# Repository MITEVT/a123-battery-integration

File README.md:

# a123-battery-integration
Battery Management System for A123 Battery-Brusa Charger combination.
## Target
NXP LPC11Cxx series ARM Cortex-M0
## Description
Interfaces between A123 Module CAN Bus and Brusa CAN Bus and sets appropriate voltage and current profiles. Essentially a battery control module.
### Referenced Library Files
* [EVT's LPC11xx Library](https://github.com/MITEVT/lpc11cx4-library)
* [Unity](https://github.com/ThrowTheSwitch/Unity)

### Requirements
```
gcc-arm-none-eabi
doxygen
oclint
```

### Looking for Examples?
* [EVT's LPC11xx Library](https://github.com/MITEVT/lpc11cx4-library)

### Trying to configure sysinit.c?
Use CMSIS Configuration Wizard v0.0.6
* http://helmpcb.com/software/cmsis-configuration-wizard
* https://sourceforge.net/projects/cmsisconfig/

## More info about our team
http://web.mit.edu/evt/

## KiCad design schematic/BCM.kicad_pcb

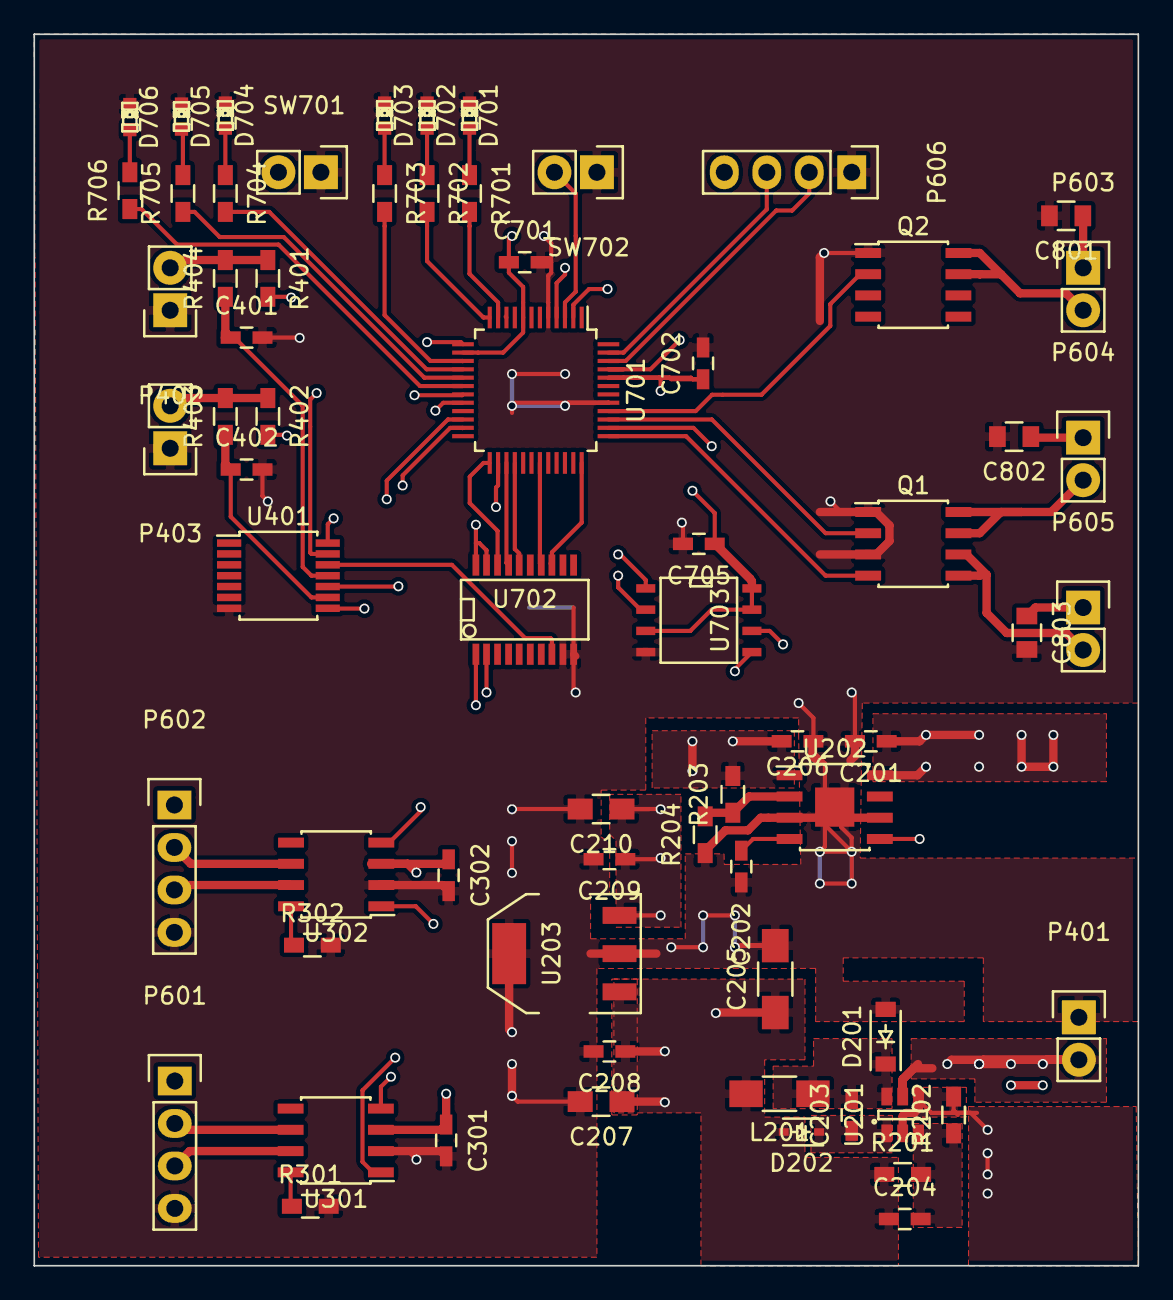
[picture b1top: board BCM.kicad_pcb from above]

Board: 4 copper layers, 66.0 x 73.7 mm, 67 parts (0 on the bottom side), 59 nets.

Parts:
C201, C206, C401, C402: 1uF; C_0603_HandSoldering
C202: 10nF; C_0603_HandSoldering
C203: 0.22pF; C_0603_HandSoldering
C204: 10pF; C_0603_HandSoldering
C205: 100uF; C_1206_HandSoldering
C207, C210: 10u; C_0805_HandSoldering
C208, C209, C701, C702: 100n; C_0603_HandSoldering
C301, C302, C705: 0.1uF; C_0603_HandSoldering
C801, C802, C803: 10uF; C_0805
D201: MBR0540; SOD-123
D202: CMDSH-3; SOD-323
D701, D702, D703, D704, D705, D706: RED; LED-0603
L201: 47uH; C_1206_HandSoldering
P401: POWERCON; Pin_Header_Straight_1x02
P402: KEYSWITCH; Pin_Header_Straight_1x02
P403: CHARGESW; Pin_Header_Straight_1x02
P601: BRUSA_CANCON; Pin_Header_Straight_1x04
P602: A123_CANCON; Pin_Header_Straight_1x04
P603: CON+; Pin_Header_Straight_1x02
P604: CON-; Pin_Header_Straight_1x02
P605: CONPRE; Pin_Header_Straight_1x02
P606: UART; Pin_Header_Straight_1x04
Q1, Q2: IRF7101PbF; SOIC-8_3.9x4.9mm_Pitch1.27mm
R201: 1M; R_0603_HandSoldering
R202: 604K; R_0603_HandSoldering
R203: 88.7k; R_0603_HandSoldering
R204: 10k; R_0603_HandSoldering
R301, R302: 33k; R_0603_HandSoldering
R401, R402, R403, R404: 20k; R_0603_HandSoldering
R701, R702, R703, R704, R705, R706: 1k; R_0603_HandSoldering
SW701: ISP; Pin_Header_Straight_1x02
SW702: RESET; Pin_Header_Straight_1x02
U201: LT1934; SOT-23-6
U202: ADP7105; SOIC-8-1EP_3.9x4.9mm_Pitch1.27mm
U203: SPX2920M3-3.3; SOT-223
U301, U302: MCP2551-I/SN; SOIC-8_3.9x4.9mm_Pitch1.27mm
U401: 74LS14; TSSOP-14_4.4x5mm_Pitch0.65mm
U701: LPC11C14; LQFP-48_7x7mm_Pitch0.5mm
U702: MCP2515_TSSOP; SSOP-20
U703: AT25XX; SOIC-8-N

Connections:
+3V3: C209.1, C210.1, C701.1, C702.1, C705.1, R401.2, R402.2, U203.3, U401.14, U701.8, U701.14, U701.44, U702.19, U702.20, U703.3, U703.7, U703.8
+5V: C204.1, C205.1, C207.1, C208.1, C301.1, C302.1, D202.2, L201.2, P606.4, R201.1, U203.1, U301.3, U302.3
+12V: C206.1, P602.1, R203.1, U202.1
+15V: C201.1, C801.1, C802.1, C803.1, P401.2, P603.1, P604.1, P605.1, U201.5, U202.8
/Can transceiver/CAN1_H_I: P601.2, U301.6
/Can transceiver/CAN1_L_I: P601.3, U301.7
/Can transceiver/CAN1_RS: R301.1, U301.8
/Can transceiver/CAN1_RX: U301.4, U702.2
/Can transceiver/CAN1_TX: U301.1, U702.1
/Can transceiver/CAN2_H_I: P602.2, U302.6
/Can transceiver/CAN2_L_I: P602.3, U302.7
/Can transceiver/CAN2_RS: R302.1, U302.8
/Can transceiver/CAN2_RX: U302.4, U701.19
/Can transceiver/CAN2_TX: U302.1, U701.20
/Contactor Driver/CON+: Q2.2, U701.40
/Contactor Driver/CON+_LOW: P603.2, Q2.7, Q2.8
/Contactor Driver/CON-: Q1.2, U701.39
/Contactor Driver/CON-_LOW: P604.2, Q1.7, Q1.8
/Contactor Driver/CONPRE: Q1.4, U701.37
/Contactor Driver/CONPRE_LOW: P605.2, Q1.5, Q1.6
/Input Connectors/CHARGESWITCH_R: P403.2, R402.1, R403.2
/Input Connectors/CHARGESWITCH_RC: C402.1, R403.1, U401.9
/Input Connectors/KEYSKWITCH_RC: C401.1, R404.1, U401.11
/Input Connectors/KEYSWITCH_R: P402.2, R401.1, R404.2
/Power/5V0_BOOST: C203.1, D202.1, U201.1
/Power/5V0_FB: C204.2, R201.2, R202.1, U201.3
/Power/5V0_L: C203.2, D201.1, L201.1, U201.6
/Power/12V0_FB: R203.2, R204.1, U202.2
/Power/12V0_SS: C202.1, U202.4
/Power/EN12V0: U202.5, U701.45
/microController/CAN1_INT: U701.36, U702.13
/microController/CAN1_MISO: U701.27, U702.17
/microController/CAN1_MOSI: U701.28, U702.16
/microController/CAN1_SCK: U701.31, U702.14
/microController/CAN1_SSEL: U701.25, U702.18
/microController/CAN_OSC2: U401.12, U702.8
/microController/CHARGESWITCH_IN: U401.8, U701.22
/microController/CLKOUT: SW701.2, U401.13, U701.4
/microController/IO_LED0: R701.2, U701.11
/microController/IO_LED1: R702.2, U701.12
/microController/IO_LED2: R703.2, U701.15
/microController/IO_LED3: R704.2, U701.16
/microController/IO_LED4: R705.1, U701.17
/microController/IO_LED5: R706.1, U701.18
/microController/KEYSWITCH_IN: U401.10, U701.23
/microController/MCU_RESET: SW702.2, U701.3
/microController/MCU_RXD: P606.2, U701.46
/microController/MCU_TXD: P606.3, U701.47
/microController/PROM_MISO: U701.26, U703.2
/microController/PROM_MOSI: U701.38, U703.5
/microController/PROM_SCK: U701.13, U703.6
/microController/PROM_SSEL: U701.2, U703.1
GND: C201.2, C202.2, C205.2, C206.2, C207.2, C208.2, C209.2, C210.2, C301.2, C302.2, C401.2, C402.2, C701.2, C702.2, C705.2, C801.2, C802.2, C803.2, D201.2, D701.1, D702.1, D703.1, D704.1, D705.1, D706.1, P401.1, P402.1, P403.1, P601.4, P602.4, P606.1, Q1.1, Q1.3, Q2.1, R202.2, R204.2, R301.2, R302.2, SW701.1, SW702.1, U201.2, U201.4, U202.3, U202.6, U202.9, U203.2, U203.4, U301.2, U302.2, U401.7, U701.5, U701.41, U702.9, U702.10, U703.4
unnamed: D701.2, R701.1
unnamed: D702.2, R702.1
unnamed: D703.2, R703.1
unnamed: D704.2, R704.1
unnamed: D705.2, R705.2
unnamed: D706.2, R706.2

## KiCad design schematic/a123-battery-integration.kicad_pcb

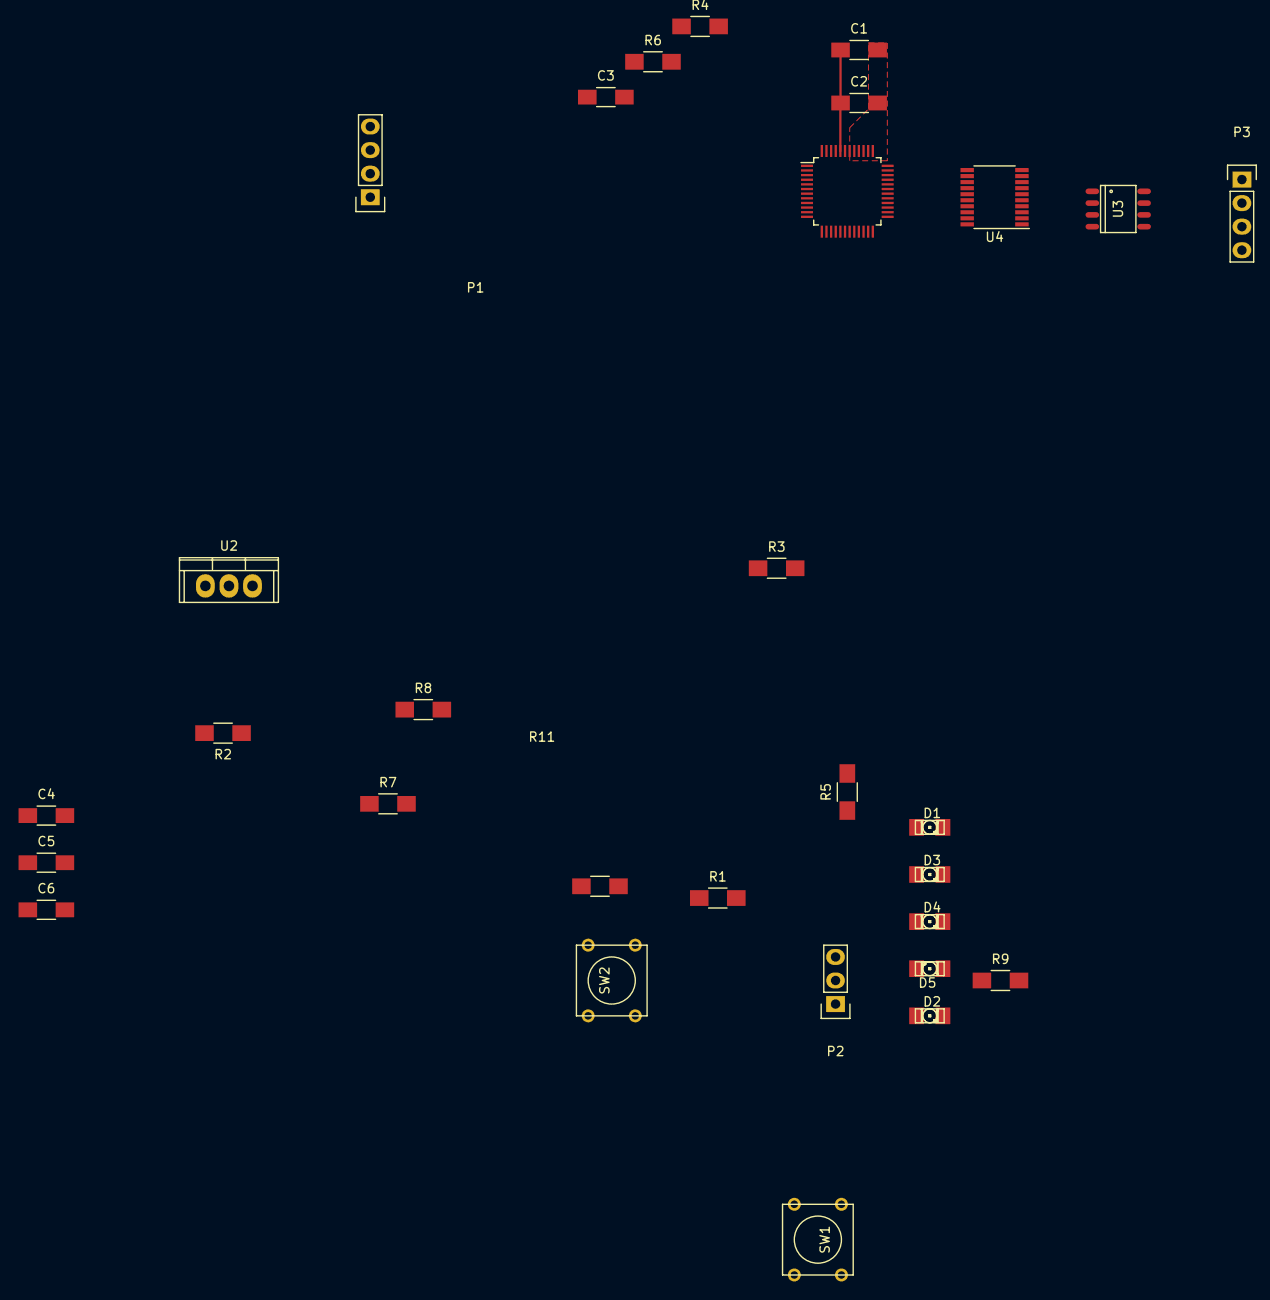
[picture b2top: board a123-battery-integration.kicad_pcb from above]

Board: 2 copper layers, 30 parts (0 on the bottom side), 30 nets.

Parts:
C1, C2, C5, C6: 10nF; C_1206_HandSoldering
C3, C4: 100nF; C_1206_HandSoldering
D1, D2, D3, D4, D5: LED; LED-1206
P1, P3: CONN_01X04; Pin_Header_Straight_1x04
P2: CONN_01X03; Pin_Header_Straight_1x03
R1: 4.7k; R_1206_HandSoldering
R2: 100; R_1206_HandSoldering
R3, R11: 120; R_1206_HandSoldering
R4, R5, R6, R7, R8: 82; R_1206_HandSoldering
R9: 10k; R_1206_HandSoldering
SW1, SW2: SW_PUSH; SW_PUSH_SMALL
U1: LPC11C24; TQFP-48_7x7mm_Pitch0.5mm
U2: LM1084IT-3.3/NOPB; TO-220
U3: ISO1050; SO-8
U4: MCP2515_TSSOP; TSSOP-20_4.4x6.5mm_Pitch0.65mm

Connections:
+3.3VP: C1.1, C2.1, C4.1, C5.1, C6.1, P1.1, R1.1, R2.1, R9.1, U1.8, U1.14, U1.17, U1.20, U1.44, U2.2, U3.1, U4.20
+5V: C3.1, U2.3
/CAN_IFACE_MISO: U1.27, U4.17
/CAN_IFACE_MOSI: U1.28, U4.16
/CAN_IFACE_SCK: U1.31, U4.14
/CAN_TRAN_RXD: U3.2, U4.2
/CAN_TRAN_TXD: U3.3, U4.1
/ISO_5V: P3.1, U3.8
/ISO_CANH: P3.2, R11.2, U3.7
/ISO_CANL: P3.3, R11.1, U3.6
/ISO_GND: P3.4, U3.5
/MCU_LED0: R5.2, U1.36
/MCU_LED1: R6.2, U1.37
/MCU_LED2: R7.2, U1.43
/MCU_LED3: R8.2, U1.48
/MCU_LED10: R4.2, U1.25
/MCU_SERIAL_RXD: P1.3, U1.46
/MCU_SERIAL_TXD: P1.4, U1.47
GND: C1.2, C2.2, C3.2, C4.2, C5.2, C6.2, D1.2, D2.2, D3.2, D4.2, D5.2, P1.2, P2.3, SW1.1, SW2.1, U1.5, U1.21, U1.22, U1.41, U2.1, U3.4, U4.10
unnamed: D1.1, R4.1
unnamed: D2.1, R5.1
unnamed: D3.1, R6.1
unnamed: D4.1, R7.1
unnamed: D5.1, R8.1
unnamed: P2.1, P2.2, R3.1, U1.18
unnamed: R1.2, SW1.2, U1.4
unnamed: R2.2, SW2.2, U1.3
unnamed: R3.2, U1.19
unnamed: R9.2, U4.19
unnamed: U1.26, U4.18

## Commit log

2015-01-18 [make] reorg
2015-01-18 Updated gitignore
2015-01-18 [make] added build directory
2015-01-18 [test] added innitial testing infrastructure
2015-01-18 [build] changed device include to be included
2015-01-26 Updated to new build system
2015-02-02 Initial A123 CAN Code Commit
2015-02-02 ported to new build
2015-02-02 Fixed make clean
2015-02-02 Running tests
2015-02-02 Fixed test build
2015-02-03 Makefile cleanup and file organization
2015-02-03 removed fake test
2015-02-03 Seperated debug printing
2015-03-07 Communicatio nbetween MCP2515 and on-chip CAN Working
2015-03-07 Added feature to auto determine ftdi comport
2015-03-15 Began laying out actual code
2015-03-23 Deleted old files
2015-03-23 Updates to overall structure and renamed some variables for clarity:
2015-03-23 Added initial contactor code
2015-03-23 Added some contactor code to charging segment
2015-03-23 Added some helper functions
2015-03-23 Moved Battery Monitoring code to Timer Interrupt
    Realized that this has to always happen, whether charging, discharging, or just idling. So why not simply increase and decrease the frequency based on mode and put it in a timer interrupt. But then t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
2015-03-23 Added a silly syntax fix
2015-03-23 Added variable frequency code and begginings of drain mode
2015-03-24 Added some useful MACROS, improved and implemented _error, began incorporating more logic
    Logic tree is beggining to take more clear form. More meetings about potential states and how to handle them are needed
2015-04-04 added first schematic
2015-04-04 Updated Charging Mode
2015-04-04 Moved around files
2015-04-04 Furtyer structural changes:
2015-04-04 test
2015-04-04 Improved structure
2015-04-04 saving status
2015-04-04 Updated stuff
2015-04-04 adding drain.h
2015-04-04 Revert "adding drain.h"
    This reverts commit c446169d240ae46f9887837304f7946d70c69991.
2015-04-04 Created initial schematic with MCU and CAN tranceivers
2015-04-04 adding drain.h v2
2015-04-04 Fix: added regulator capacitors
2015-04-04 it compiles!
2015-04-04 finished drain state machine
2015-04-04 comment drain state machine
2015-04-04 Implemented get next state
2015-04-11 [SCHEMATIC] swapped MCP2551 for ISO1050, small changes, updated package associations
2015-04-19 Added a few changes and a test, testing is broken
2015-04-25 started schematic as a higherarchy
2015-05-02 continued work on splitting the schematic
2015-05-02 Rewrote Charge statemachine and fixed tests
2015-05-02 [schematic] editing power added extra schematics
2015-05-02 added more schematic things
2015-05-02 [schematic] finished HV sense
2015-05-02 changes to microController schematic
2015-05-02 fixed connections
2015-05-02 fixed connections, updated kicad version
2015-05-02 isolation changes
2015-05-02 [schematic] more decoupling
2015-05-02 [schematic] changed micro added isolated tranceiver and cleaned
2015-05-09 Ported over Charge and Drain state machines to new unit system
2015-05-09 Added new test cases and fixed new unit system
2015-05-09 Updated gitignore for testbin
2015-05-09 Fixed balancing so that it actually balances down to 1mV, added test as well
2015-05-09 Changed contactor code and updated super state machine
2015-05-09 Fixed CAN_error bug (interrupt using msTicks hangs)
2015-05-09 added switch debouncing
2015-05-31 Updated Optimization flag and added debug statements
2015-05-31 Added A123 Tests
2015-06-01 Used GOTO to remove charge statemachine value lag
2015-06-03 Updated tests
2015-06-06 [schematic] changed stuff
2015-06-06 added contactor drive moduels and interupt pin on MCP2515
2015-06-06 [schematic] added contactor drive circuits and improved system wiring
2015-06-10 Fixed bugs including, SSP Timing errors, Incorrect Addressing
2015-06-10 Began moving over Supr State machine
2015-06-11 Updated Drain SM to follow charge sm template
2015-06-11 Moved charge sm over to new return types
2015-06-11 Ported over to new SuperStateMachine system and added tests
2015-06-11 Removed unused types
2015-06-12 [schematic] I honestly don't remember
2015-06-12 [schematic] basically finished with the schematic
2015-06-13 [schematic] selected I2C resistors
2015-06-13 [schematic] renamed can tranceiver sub schematic
2015-06-13 Latest
2015-06-13 [schematic] added lables to all input connector nodes
2015-06-13 [schematic] added labels on power sheet
2015-06-13 [schematic] added labels to CAN transceiver
2015-06-13 [schematic] modified micro controller labels
2015-06-13 [schematic] annotated all components
2015-06-13 fixed component library issue
2015-06-13 [schematic] re-added switch and net lable that were mistakenly deleted
2015-06-13 [schematic] removed last reference to +3.3VP
2015-06-14 Moved over to milli c rating and moved a123 decode out of interrupt
2015-06-18 Incororated oclint into makefile and fixed some shit
2015-06-18 Fixed Lint Long Line warning and make unity test dependant on makefile
2015-06-18 Fixed type size error and incorportated balance boolean into statemachine/struct also updated tests:
2015-06-18 Improved comments and added timed debug messages
2015-06-19 [schematic][netlist][footprint] added UART to output connectors. first pass at footprints. footprints incomplete
2015-06-19 added more packages
2015-06-19 added stack usage report to compile flags. stack usage for a file will apear in /bin/xxx.su
2015-06-20 Fixed stupid mistake where com depended on object files
2015-06-20 Updated code to properly initialize Brusa and clear latch errors
2015-06-20 Cleaned up some shit without breaking it I think
2015-06-20 Cleaned up code and potentially fixed delayed charge start bug
2015-06-20 [packages] component association
2015-06-20 replaced contactor driver MOSFETs with IRF7101PbF parts
2015-06-20 added footprint associations for 60Mhz crystal and others
2015-06-20 initial layout commit
2015-06-20 Added staged updating and fixed turn off bug. Tested and charging fucign works
2015-06-20 layout: most parts done, fill zones in progress
2015-06-26 Cleaned up code and added documentation with doxygen
2015-06-27 Fleshed out readme
2015-06-27 Moved Brusa decode over to the library
2015-06-27 [layout] went to 4 layers nearly done
2015-06-27 Created a pack manager for staged updates and moved configuration information to config.h
2015-07-01 Cleaned up code, modified charge sm, and added tests
2015-07-01 [routing] finished routing passed all DRCs moved pins to accomodate routing
2015-07-11 Added Comments
2015-07-21 Updated gitignore for dia file
2015-07-21 Removed some bullshit
2015-07-21 Final change before fab
2015-12-19 remove swp file
2015-12-19 correct swp changes
2016-03-05 Added balance state for balancing a123 modules
2017-02-12 Fixed compilation errors stemming from updated lpc_libs
